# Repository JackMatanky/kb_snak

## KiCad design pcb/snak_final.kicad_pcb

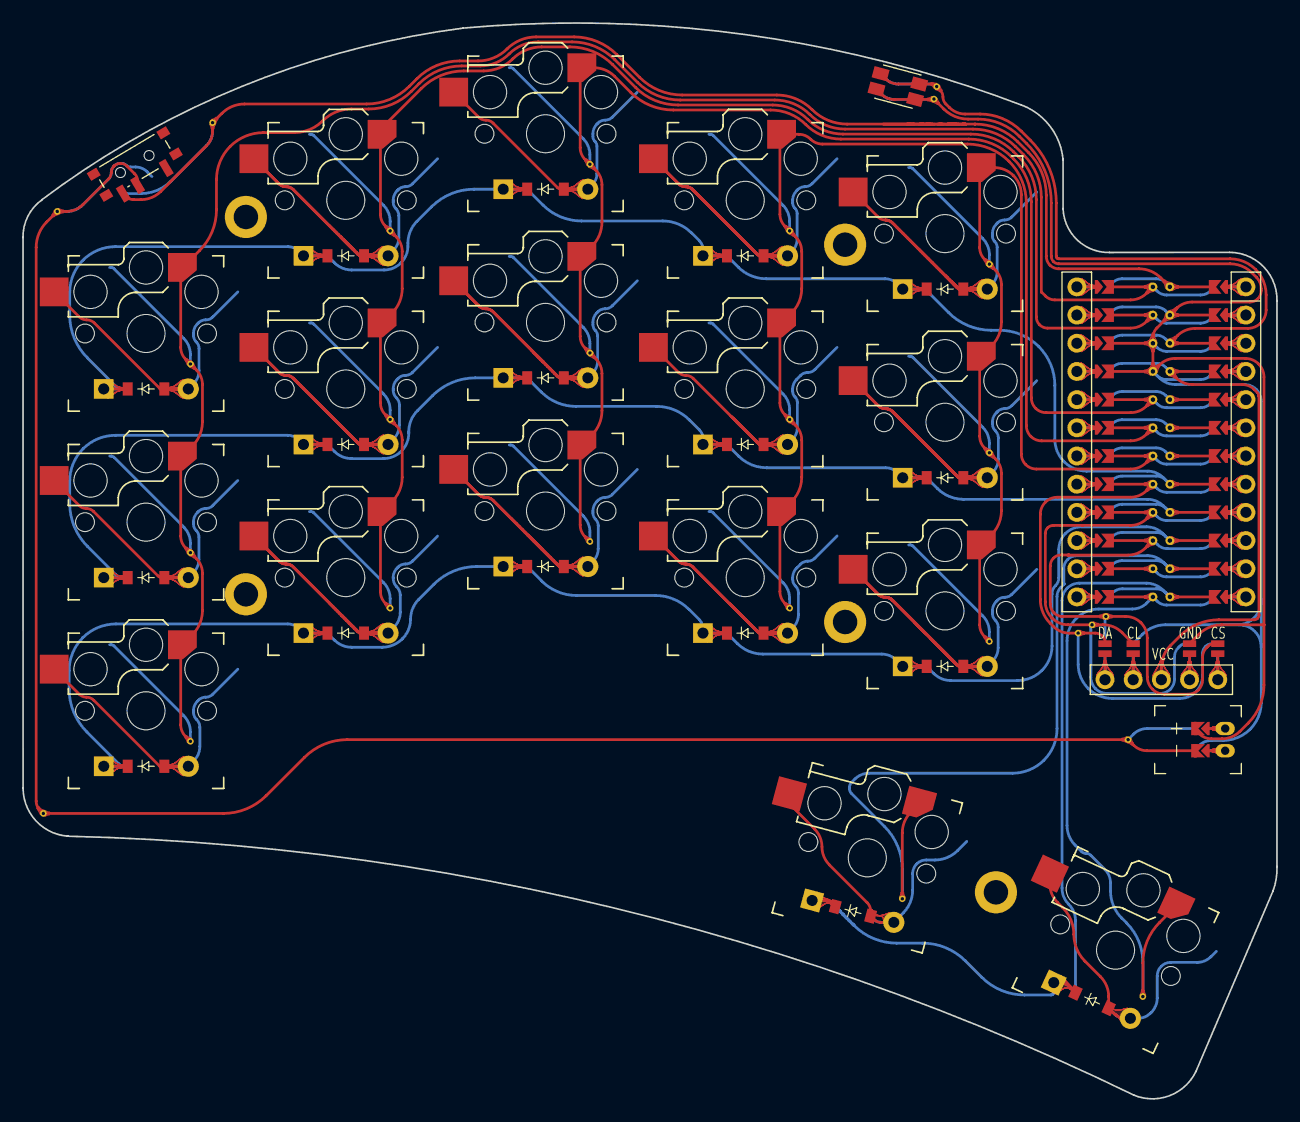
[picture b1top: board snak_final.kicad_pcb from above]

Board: 2 copper layers, 113.0 x 96.9 mm, 44 parts (0 on the bottom side), 42 nets.

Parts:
D1, D2, D3, D4, D5, D6, D7, D8, D9, D10, D11, D12, D13, D14, D15, D16, D17: ComboDiode
DISP1: nice!view
H1, H2, H3, H4, H5: mounting_hole
JST1: JST_PH_S2B-PH-K
MCU1: nice_nano
S1, S2, S3, S4, S5, S6, S7, S8, S9, S10, S11, S12, S13, S14, S15, S16, S17: PG1350
SW1: sw_reset_side
SW2: power_switch

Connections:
DISP1_1: DISP1.1, DISP1.10, DISP1.23
DISP1_2: DISP1.2, DISP1.11, DISP1.22
DISP1_4: DISP1.4, DISP1.12, DISP1.21
DISP1_5: DISP1.5, DISP1.13, DISP1.20
GND: DISP1.16, DISP1.26, JST1.1, MCU1.103, MCU1.104, MCU1.123, SW1.1
JST1_1: JST1.11, JST1.21, JST1.31
JST1_2: JST1.12, JST1.22, JST1.32
P0: MCU1.102, S4.1, S5.1, S6.1
P1: MCU1.101, S1.1, S2.1, S3.1
P2: MCU1.105, S7.1, S8.1, S9.1
P3: MCU1.106, S10.1, S11.1, S12.1
P4: MCU1.107, S13.1, S14.1, S15.1
P5: DISP1.14, DISP1.24, MCU1.108
P6: DISP1.15, DISP1.25, MCU1.109
P7: DISP1.17, DISP1.27, MCU1.110
P9: MCU1.112, S17.1
P10: D16.1, D17.1, MCU1.113
P14: D1.1, D4.1, D7.1, D10.1, D13.1, MCU1.115
P15: D2.1, D5.1, D8.1, D11.1, D14.1, MCU1.116
P16: MCU1.114, S16.1
P18: D3.1, D6.1, D9.1, D12.1, D15.1, MCU1.117
RAW: MCU1.124, SW2.3, SW2.6
RST: MCU1.122, SW1.2
VCC: DISP1.3, MCU1.121
in_home: D17.2, S17.2
index_bot: D10.2, S10.2
index_mid: D11.2, S11.2
index_top: D12.2, S12.2
inner_bot: D13.2, S13.2
inner_mid: D14.2, S14.2
inner_top: D15.2, S15.2
middle_bot: D7.2, S7.2
middle_mid: D8.2, S8.2
middle_top: D9.2, S9.2
out_home: D16.2, S16.2
pinky_bot: D1.2, S1.2
pinky_mid: D2.2, S2.2
pinky_top: D3.2, S3.2
pos: JST1.2, SW2.2, SW2.5
ring_bot: D4.2, S4.2
ring_mid: D5.2, S5.2
ring_top: D6.2, S6.2

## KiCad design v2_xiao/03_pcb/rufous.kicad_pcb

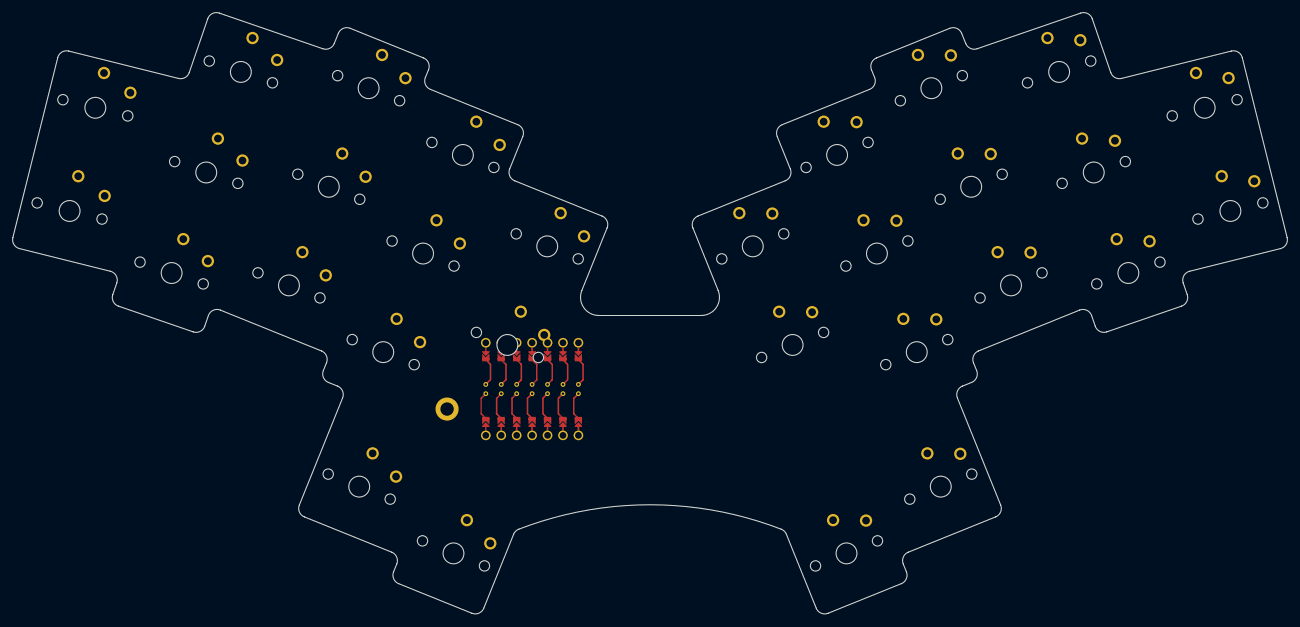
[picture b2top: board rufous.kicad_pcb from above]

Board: 2 copper layers, 209.8 x 99.0 mm, 32 parts (0 on the bottom side), 11 nets, no tracks yet.

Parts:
H1: mounting_hole
S1, S2, S3, S4, S5, S6, S7, S8, S9, S10, S11, S12, S13, S14, S15, S16, S17, S18, S19, S20, S21, S22, S23, S24, S25, S26, S27, S28, S29, S30: PG1350
xiao-ble1: ProMicro; xiao-ble

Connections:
P0: S2.1, S8.1, S13.1, S18.1, S24.1, xiao-ble1.24
P1: S5.1, S11.1, S15.1, S21.1, S26.1, xiao-ble1.23
P2: S1.1, S7.1, S12.1, S17.1, S23.1, xiao-ble1.22
P3: S4.1, S10.1, S14.1, S20.1, S25.1, xiao-ble1.21
P4: S3.1, S9.1, S19.1, S28.1, S29.1, xiao-ble1.20
P5: S6.1, S16.1, S22.1, S27.1, S30.1, xiao-ble1.19
P6: S1.2, S2.2, S3.2, S4.2, S5.2, S6.2, xiao-ble1.18
P7: S7.2, S8.2, S9.2, S10.2, S11.2, S27.2, xiao-ble1.7
P8: S12.2, S13.2, S22.2, S25.2, S26.2, S28.2, xiao-ble1.6
P9: S16.2, S19.2, S20.2, S21.2, S23.2, S24.2, xiao-ble1.5
P10: S14.2, S15.2, S17.2, S18.2, S29.2, S30.2, xiao-ble1.4
